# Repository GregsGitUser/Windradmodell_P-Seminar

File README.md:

# Windradmodell_P-Seminar
CAD-Dateien der von mir erstellten Teile und der Code, der auf dem Arduino Nano läuft. Außerdem noch die source-Dateien für die Platine, die ich für dieses Projekt gemacht habe

Im Rahmen des P-Seminars Physik am ITG 2020-22 mit dem Thema Klimawandel

Wir wollten ein Windradmodell bauen und an diesem verschiedene Messungen durchführen. Als Zusatzfunktion sollte es noch der Windrichtung folgen,
was durch einen Schrittmotor (NEMA 17-03 mit 20Nm und 0,2A) in der Basis des Windrads und einen Zweipunktregler möglich wurde. Zur Ansteuerung wird ein A4988 Treiber verwendet.
Der Microcontroller ist ein Arduino Nano, der als Interface einen Drehenkoder (KY-040) und Kippschalter hat. So kann auch die Regelungsgeschwindigkeit für den Zweipunktregler
eingestellt werden. Informationen können auf einem 16x2 LCD-Bildschirm abgelesen werden, der über I2c (mit I2c Bus) mit dem Microcontroller kommuniziert. 
Ein generisches Gleichstromnetzteil dient als Stromversorgung.

Oben in der Gondel des Windrads ist ein kleiner Generator, dessen Ausgangsleistung an einem Lastwiderstand (>2 Ohm) abfällt.
Die Spannung, welche über dem Widerstand abfällt, kann direkt analog mit dem internen 10-Bit ADC eingelesen werden, weil sie 5V (die Logikspannung des Nanos) nie überschreitet.
Aus diesen Werten kann die insgesamte elektrische Leistung abgeleitet werden. (meistens unter 200mW)

Eine andere Möglichkeit, die Leistung zu bestimmen ist mittels der detektierten Rotorblätter. Am Mast sitz ein HC-SR04 Ultraschallsensor, der zeitgleich in 5-Sekunden Intervallen
die Rotorblätter zählt und das Ergebnis dann auf dem LCD ausgibt. So kann die auf zwei Arten gemessene Leistung verglichen werden.

Alle hier aufgelisteten 3d-Modelle habe ich in Autodesk Fusion 360 oder SOLIDWORKS designed und auf einem Prusa Mk2 gedruckt. Das Design der Platine habe ich in 
Autodesk EAGLE erstellt und diese anschließend mit dem PCB-GCODE ulp-plugin zuhause gefertigt. Der Arduino Nano wurde mit der Arduino IDE programmiert.
Die Aluteile, die Propellernaben für unterschiedlich viele Rotorblätter, und die Basis für den Schrittmotor haben wir in Kooperation mit Autoliv gefertigt.

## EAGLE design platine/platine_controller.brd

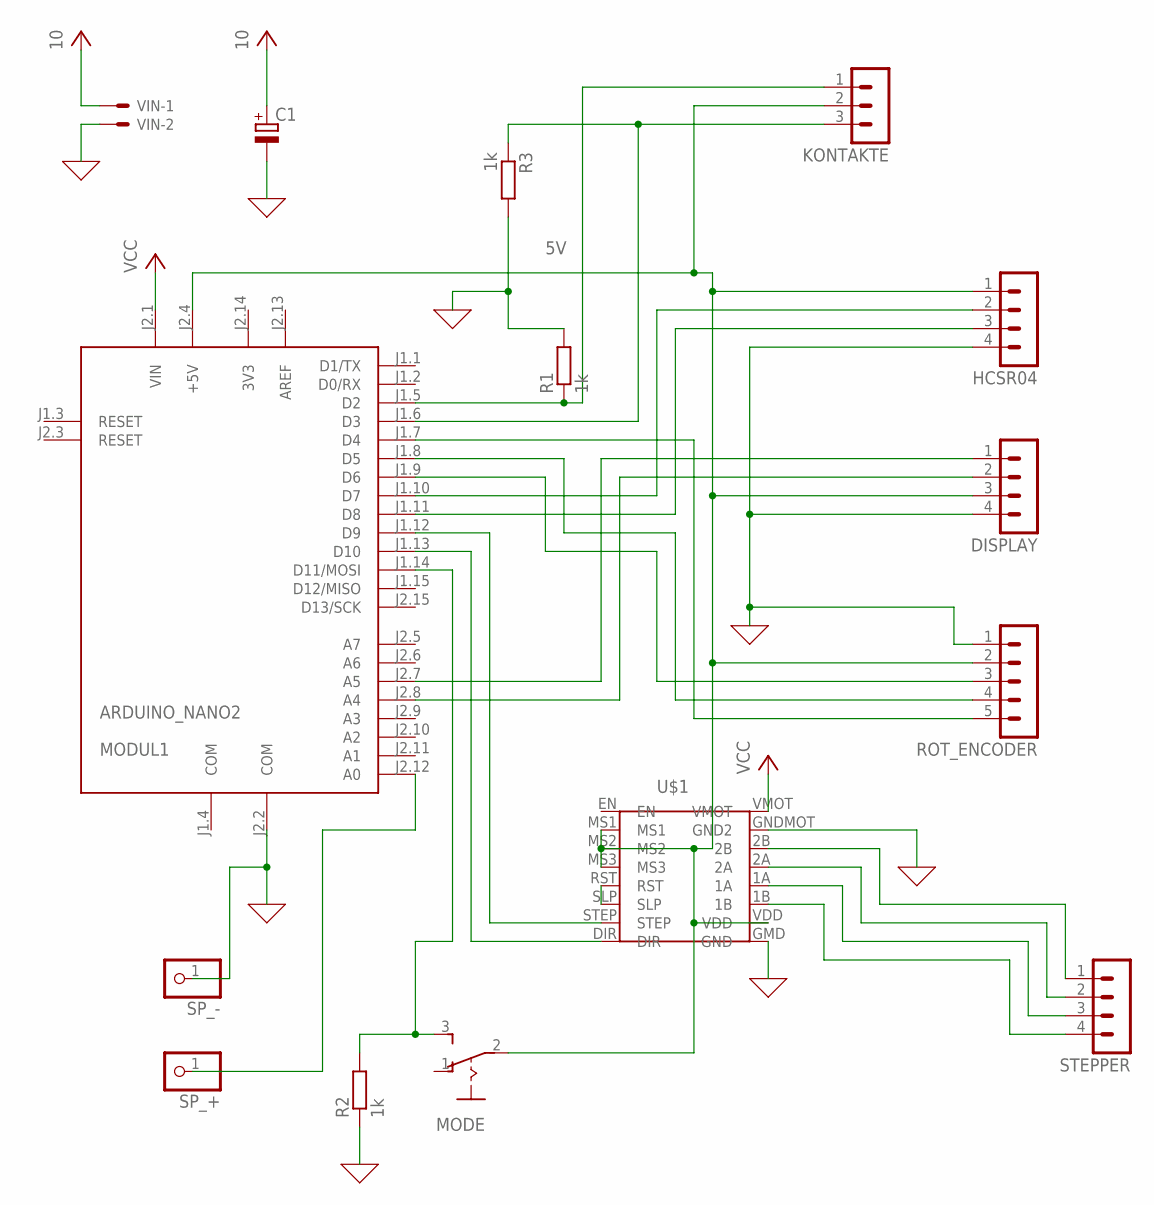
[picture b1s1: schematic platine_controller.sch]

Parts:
C1: CPOL-EUE2,5-6E; E2,5-6E
DISPLAY: MA04-1
HCSR04: MA04-1
KONTAKTE: MA03-1
MODE: 255SB
MODUL1: ARDUINO_NANO2
R1, R2, R3: 1k; 0207/10
ROT_ENCODER: MA05-1
SP_+: PINHD-1X1; 1X01
SP_-: PINHD-1X1; 1X01
STEPPER: MA04-1
U$1: A4988
VIN: 22-23-2021

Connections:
3V3: MODUL1.J2.14 (3V3)
5V: DISPLAY.3, HCSR04.1, KONTAKTE.2, MODE.2, MODUL1.J2.4 (+5V), ROT_ENCODER.2, U$1.MS1, U$1.MS2, U$1.MS3, U$1.VDD
AREF: MODUL1.J2.13 (AREF)
COM: C1.-, DISPLAY.4, HCSR04.4, MODUL1.J1.4 (COM), MODUL1.J2.2 (COM), R1.2, R2.1, R3.2, ROT_ENCODER.1, SP_-.1, U$1.GMD (GND), U$1.GNDMOT (GND2), VIN.2
unnamed: MODUL1.J1.7 (D4), ROT_ENCODER.5
unnamed: STEPPER.1, U$1.2B
unnamed: MODUL1.J1.12 (D9), U$1.STEP
unnamed: MODUL1.J1.13 (D10), U$1.DIR
unnamed: U$1.RST, U$1.SLP
unnamed: STEPPER.2, U$1.2A
unnamed: STEPPER.3, U$1.1A
unnamed: STEPPER.4, U$1.1B
unnamed: HCSR04.3, MODUL1.J1.11 (D8)
unnamed: HCSR04.2, MODUL1.J1.10 (D7)
unnamed: DISPLAY.1, MODUL1.J2.7 (A5)
unnamed: DISPLAY.2, MODUL1.J2.8 (A4)
unnamed: MODUL1.J1.9 (D6), ROT_ENCODER.3
unnamed: MODUL1.J1.8 (D5), ROT_ENCODER.4
unnamed: KONTAKTE.3, MODUL1.J1.6 (D3), R3.1
unnamed: KONTAKTE.1, MODUL1.J1.5 (D2), R1.1
unnamed: MODE.3 (S), MODUL1.J1.14 (D11/MOSI), R2.2
unnamed: MODUL1.J2.12 (A0), SP_+.1
VCC: C1.+, MODUL1.J2.1 (VIN), U$1.VMOT, VIN.1

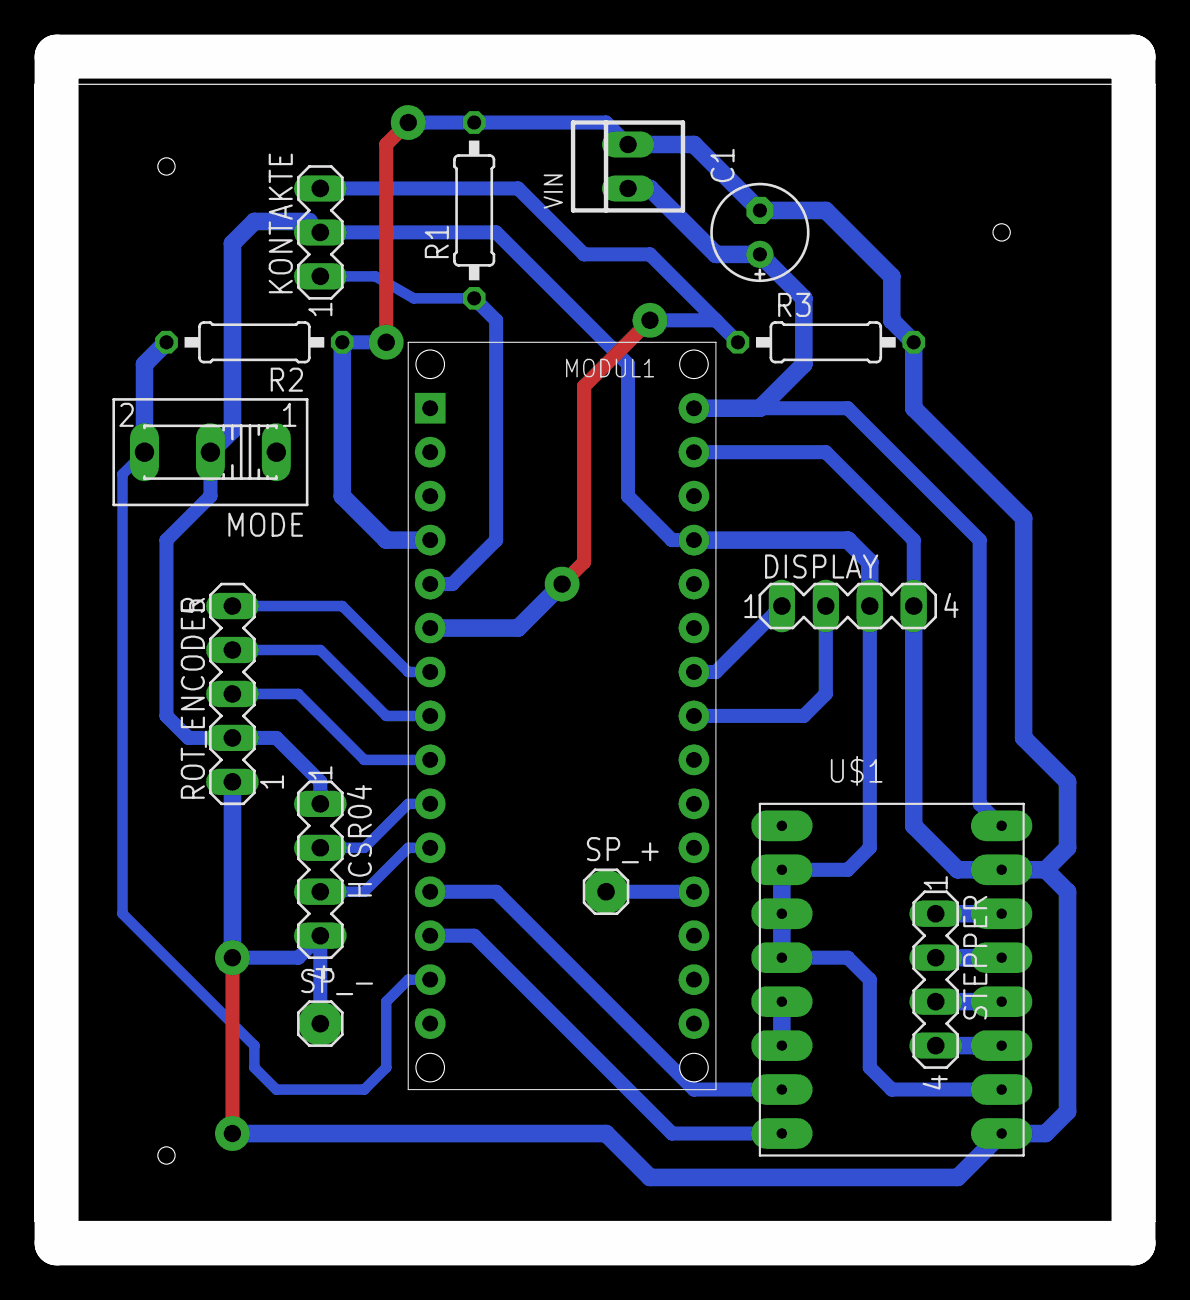
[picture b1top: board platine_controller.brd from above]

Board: 2 copper layers, 62.2 x 68.6 mm, 15 parts (0 on the bottom side), 21 nets.

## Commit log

2021-10-28 platinenlayout .brd und .sch plus PNG
    wurden in Autodesk EAGLE erstellt
2021-10-28 auf dem arduino nano laufender programmcode
    grundlegend C++
    kann mit der Arduino IDE geöffnet werden
2021-10-28 Plan für die Gondel
